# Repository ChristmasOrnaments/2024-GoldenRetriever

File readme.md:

Christmas ornament number 12...

***

The detailed explanation of the original Snowman ornament is [here](https://github.com/ChristmasOrnaments/2013-Snowman).

This ornament shares the same schematic and code base as the previous ornaments. Obviously the silkscreen image and LED locations have changed.  

### Compiling

* Install [ATTinyCore](https://github.com/spencekonde/attinycore) using the boards manager
* Select **Attiny25/45/85 (No bootloader)** from the boards list
* Set the *Clock source* to **8MHz (internal)** (Code uses a prescalar of 2 to lower it to 4MHz)
* Set *B.O.D* to **Disabled**
* Select **Burn Bootloader** to write the changes
* Compile and write the program to the MCU

If using another method to program the MCU, just remember you need to set the fuses properly both for correct speed and for the power saving features. The fuses (for an ATTINY85) should be:

Low: 62  
High: DF  
Extended: FF

You can see the effect of different fuse settings (and their values) [here](http://www.engbedded.com/fusecalc/).

### Resources

**Charlieplexing Code using a byte array:**  
[https://www.instructables.com/CharliePlexed-LED-string-for-the-Arduino/](https://www.instructables.com/CharliePlexed-LED-string-for-the-Arduino/)

**Battery calculator:**  
[http://oregonembedded.com/batterycalc.htm](http://oregonembedded.com/batterycalc.htm)

**Power saving information:**  
[http://www.gammon.com.au/forum/?id=11497](http://www.gammon.com.au/forum/?id=11497)  
[http://www.insidegadgets.com/2011/02/05/reduce-attiny-power-consumption-by-sleeping-with-the-watchdog-timer](http://www.insidegadgets.com/2011/02/05/reduce-attiny-power-consumption-by-sleeping-with-the-watchdog-timer/)  
[http://www.nongnu.org/avr-libc/user-manual/group\_\_avr\_\_power.html](http://www.nongnu.org/avr-libc/user-manual/group__avr__power.html)

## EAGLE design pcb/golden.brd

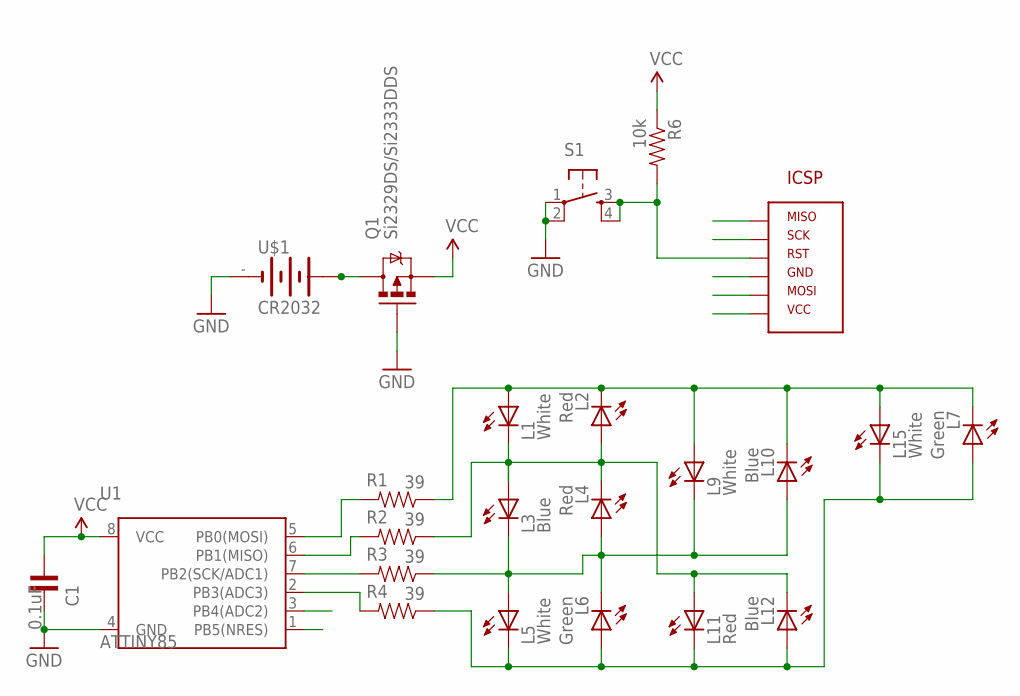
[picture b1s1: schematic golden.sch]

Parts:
C1: 0.1uF; C0805
L1, L5, L9, L15: White; LED-0805
L2, L4, L11: Red; LED-0805
L3, L10, L12: Blue; LED-0805
L6, L7: Green; LED-0805
Q1: Si2329DS/Si2333DDS; SOT23-3A
R1, R2, R3, R4: 39; R0805
R6: 10k; R0805
S1: TAC_SWITCHSMD; TACTILE_SWITCH_SMD
U1: ATTINY85; SOIC-8
U$1: CR2032; BAT-HLD-001
U$2: AVR_ICSP_6P1X6; AVR_ICSP_1X6_SMD

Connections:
GND: C1.2, Q1.1 (G), S1.1, S1.2, U1.4 (GND), U$1.-, U$2.P6 (GND)
L12: L1.C, L2.A, L3.A, L4.C, L11.A, L12.C, R2.1
MISO: R2.2, U1.6 (PB1(MISO)), U$2.P5 (MISO)
MOSI: R1.2, U1.5 (PB0(MOSI)), U$2.P4 (MOSI)
unnamed: Q1.3 (D), U$1.+@1 (+), U$1.+@2 (+)
unnamed: L3.C, L4.A, L5.A, L6.C, L9.C, L10.A, R3.1
unnamed: R4.2, U1.2 (PB3(ADC3))
unnamed: L1.A, L2.C, L7.C, L9.A, L10.C, L15.A, R1.1
unnamed: L5.C, L6.A, L7.A, L11.C, L12.A, L15.C, R4.1
RST: R6.2, S1.3, S1.4, U1.1 (PB5(NRES)), U$2.P3 (RST)
SCK: R3.2, U1.7 (PB2(SCK/ADC1)), U$2.P2 (SCK)
VCC: C1.1, Q1.2 (S), R6.1, U1.8 (VCC), U$2.P1 (VCC)

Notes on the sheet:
ICSP

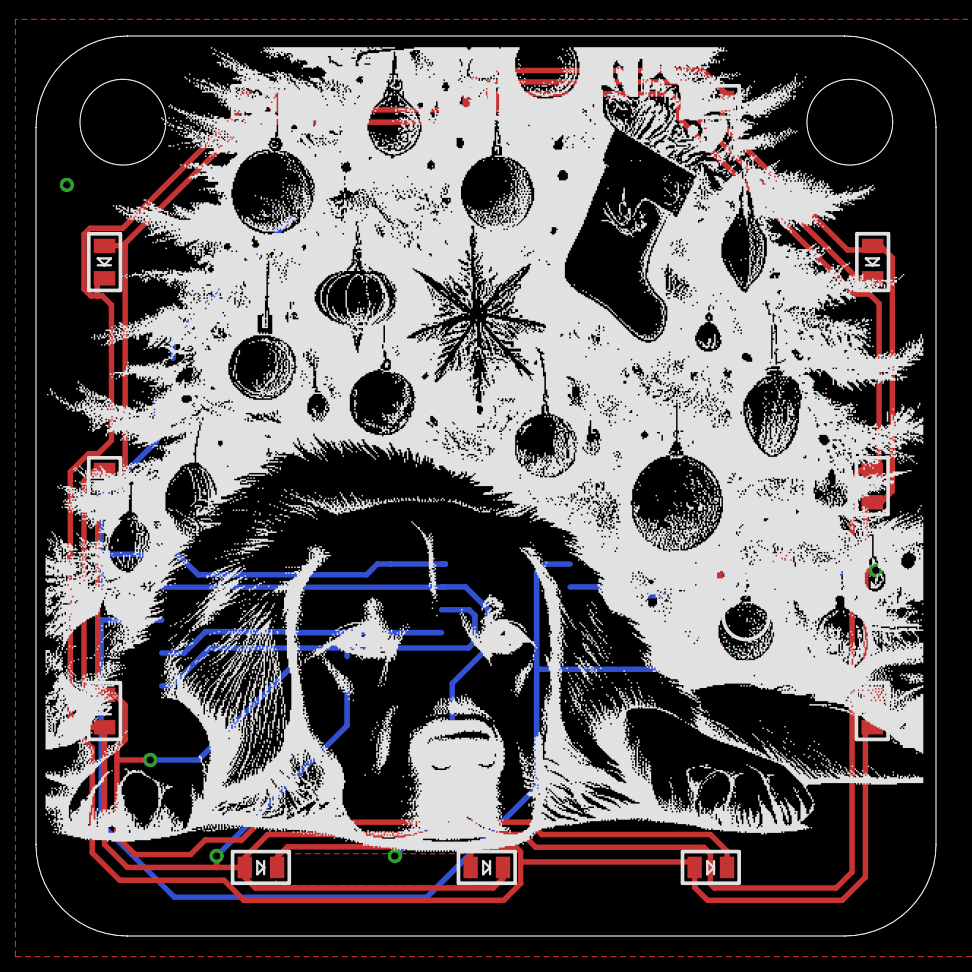
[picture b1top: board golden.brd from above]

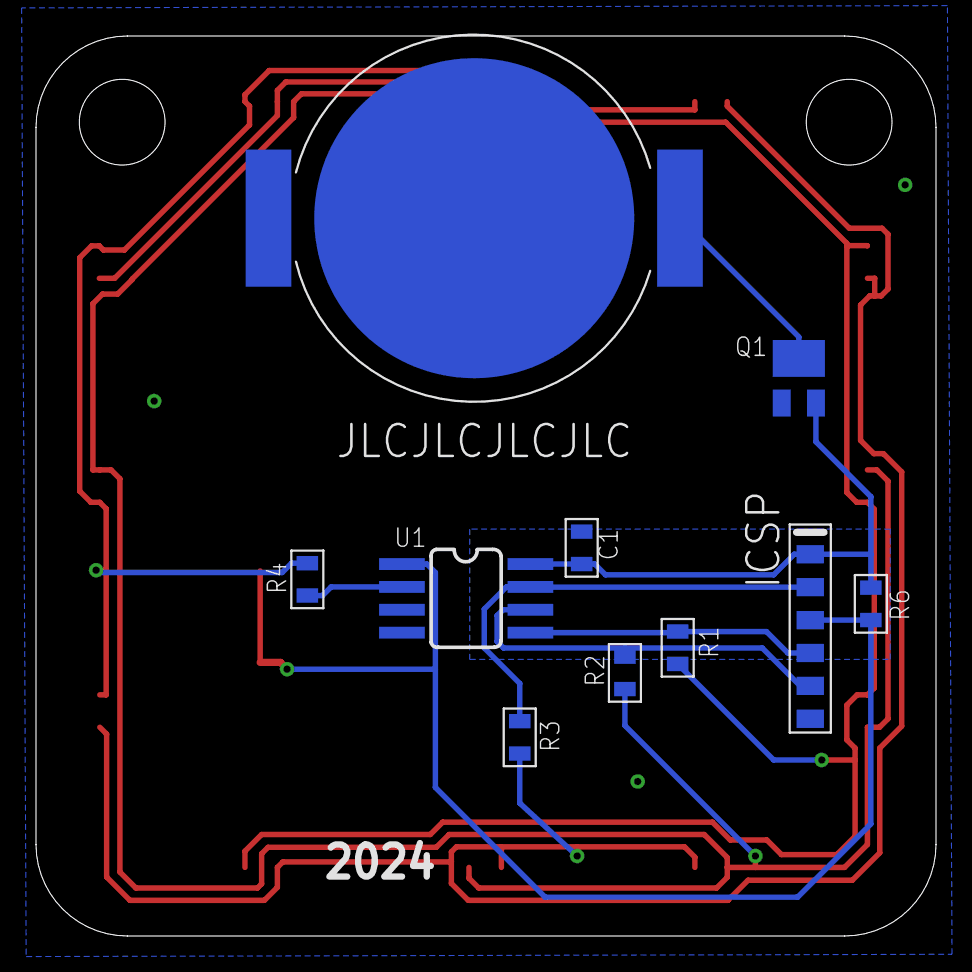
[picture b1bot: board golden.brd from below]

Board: 2 copper layers, 50.0 x 50.0 mm, 23 parts (10 on the bottom side), 12 nets.

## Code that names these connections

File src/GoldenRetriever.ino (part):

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
// ATMEL ATTINY85 / ARDUINO
//	            						  ____
//  		   (D5/A0) RST/PB5	1|*	  |8  VCC
//	 PWM   (D3/A3)	   PB3	2|	  |7  PB2  (D2/A1)
//	 PWM   (D4/A2)	   PB4	3|	  |6  PB1  (D1)		PWM
//	        				   GND	4|____|5  PB0  (D0)		PWM

#include <avr/pgmspace.h>
// Power Mgt:
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
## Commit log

2026-03-22 init
2026-03-22 added animated gif

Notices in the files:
parts and their libraries:
SparkFun: Licensing: CC v3.0 Share-Alike You are welcome to use this library for commercial purposes.
